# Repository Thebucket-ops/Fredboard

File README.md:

# ***THE FREDBOARD V1/V2***
fred is the seal

  The fredboard is a custom pi pico devboard:
  - the v2 has a MPU-6500 and has a reboot button with a led to indicate the restart;
  - the v1 (untested) allows to use all but one pins provided by the rp2040, and has a led to indicate when the devboard is powered

## **V2 (TO BE APPROVED)**

(Fred is the sea lion)

### **SCHEMATICS**
  Here's the schematic for the pcb, you can see the whole project from /v2/PCB

### **THE PCB**
  This is the pcb, front and back (image art can be found on /img/devboard):

### **PINOUT**
  Here's a diagram for the pinout of the v2, for more information on each pins capabilities, look up the rp2040 datasheet

### **BOM and Gerber**
  The Bill Of Materials and the Gerber files can be found in the /v2/PCB/production folder, these are the required materials:

 - 2 33pF 0402 capacitors
 - 13 0.1uF 0402 capacitors
 - 2 1uF 0402 capacitors
 - 2 10uF 0603 capacitors
 - 1 10 nF 0402 capacitor
 - 1 0402 white led
 - 1 USB_C_Receptacle_USB2.0_14P
 - 2 pinheaders 1x20 (optional)
 - 1 pinheader 1x3 (optional)
 - 2 0402 27 ohm resistors
 - 1 0402 150 ohm resistor
 - 3 0402 1K resistors
 - 2 0402 5.1K resistors
 - 1 0402 10K resistor
 - 2 SW_Push_SPST_NO_Alps_SKRK button
 - 1 RP2040
 - 1 MCP1700x-330xxTT
 - 1 W25Q16JVUXIQ TR flash memory
 - 1 Crystal_SMD_3225-4Pin_3.2x2.5mm
 - 1 MPU-6500

## **V1 (UNTESTED)**

### **SCHEMATICS**
  Here's the schematic for the pcb, you can see the whole project from /PCB

### **THE PCB**
  This is the pcb, front and back (image art can be found on /img/devboard):

### **BOM and Gerber**
  The Bill Of Materials and the Gerber files can be found in the /PCB/production folder, these are the required materials:

 - 10 0.1uF 0402 capacitors
 - 2 1uF 0402 capacitors
 - 2 10uF 0603 capacitors
 - 2 33pF 0402 capacitors
 - 1 0402 white led
 - 1 USB_C_Receptacle_USB2.0_14P
 - 2 pinheaders 1x20 (optional)
 - 1 pinheader 1x3 (optional)
 - 2 0402 5.1K resistors
 - 2 0402 27 ohm resistors
 - 2 0402 1K resistors
 - 1 0402 10K resistor
 - 1 SW_Push_SPST_NO_Alps_SKRK button
 - 1 RP2040
 - 1 MCP1700x-330xxTT
 - 1 W25Q16JVUXIQ TR flash memory
 - 1 Crystal_SMD_3225-4Pin_3.2x2.5mm

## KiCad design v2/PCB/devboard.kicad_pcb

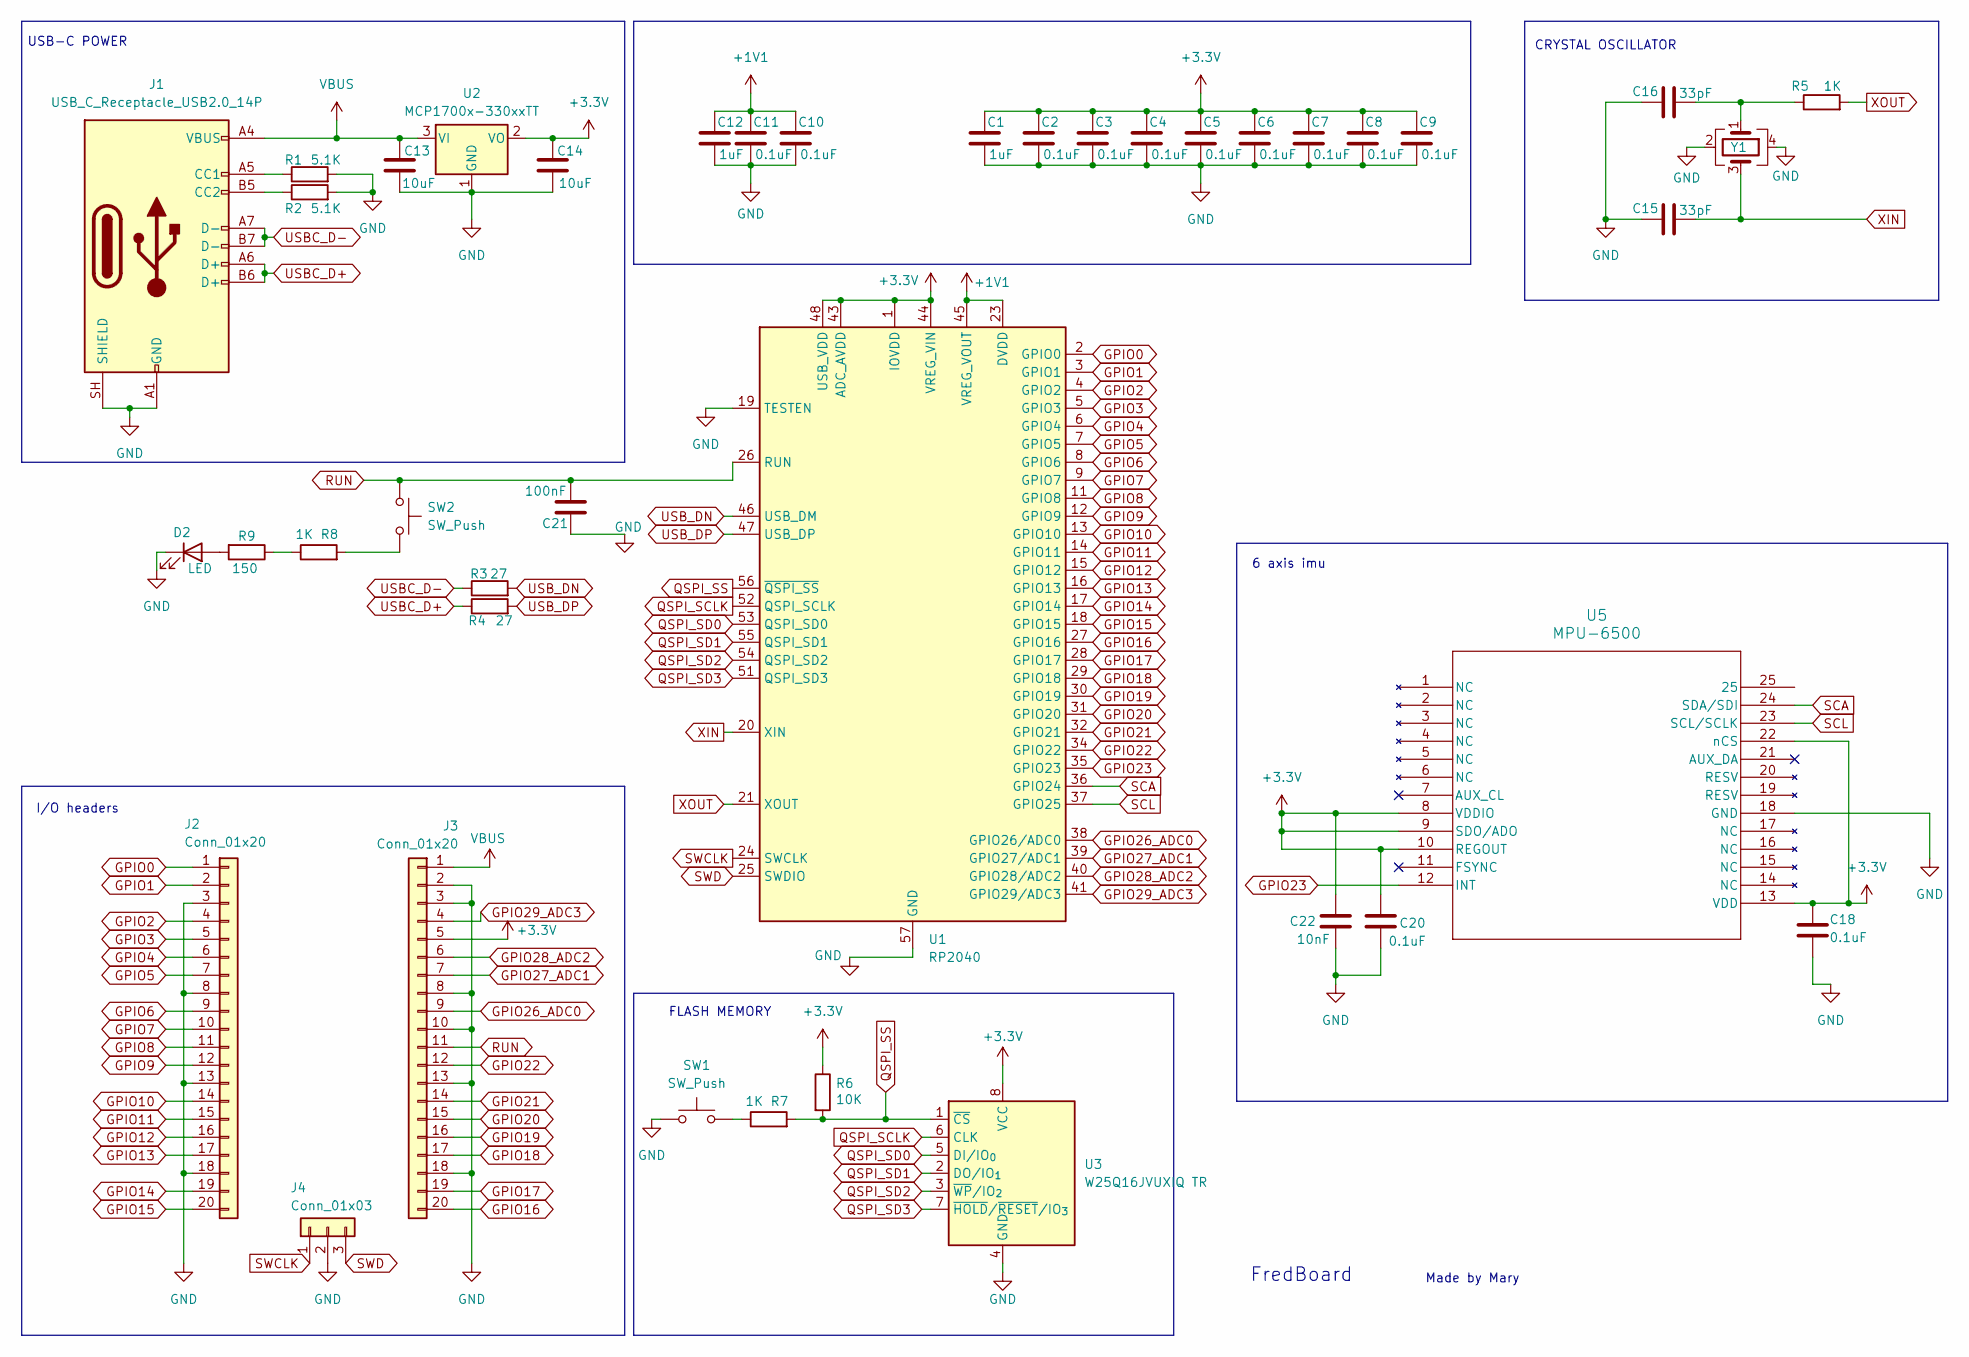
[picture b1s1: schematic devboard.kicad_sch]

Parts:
C1, C12: 1uF; C_0402_1005Metric
C2, C3, C4, C5, C6, C7, C8, C9, C10, C11, C18, C20: 0.1uF; C_0402_1005Metric
C13, C14: 10uF; C_0603_1608Metric
C15, C16: 33pF; C_0402_1005Metric
C21: 100nF; C_0402_1005Metric
C22: 10nF; C_0402_1005Metric
D2: LED; LED_0402_1005Metric
J1: USB_C_Receptacle_USB2.0_14P; USB_C_Receptacle_HRO_TYPE-C-31-M-12
J2, J3: Conn_01x20; PinHeader_1x20_P2.54mm_Vertical
J4: Conn_01x03; PinHeader_1x03_P2.54mm_Vertical
R1, R2: 5.1K; R_0402_1005Metric
R3, R4: 27; R_0402_1005Metric
R5, R7, R8: 1K; R_0402_1005Metric
R6: 10K; R_0402_1005Metric
R9: 150; R_0402_1005Metric
SW1, SW2: SW_Push; SW_Push_SPST_NO_Alps_SKRK
U1: RP2040; QFN-56-1EP_7x7mm_P0.4mm_EP3.2x3.2mm
U2: MCP1700x-330xxTT; SOT-23
U3: W25Q16JVUXIQ TR; Winbond_USON-8-1EP_3x2mm_P0.5mm_EP0.2x1.6mm
U5: MPU-6500; QFN24_3X3X0P9_IVS
Y1: Crystal_GND24; Crystal_SMD_3225-4Pin_3.2x2.5mm

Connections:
+1V1: C10.1, C11.1, C12.1, U1.23 (DVDD), U1.45 (VREG_VOUT), U1.50 (DVDD)
+3.3V: C1.1, C2.1, C3.1, C4.1, C5.1, C6.1, C7.1, C8.1, C9.1, C14.1, C18.1, C20.1, C22.1, J3.5, R6.1, U1.1 (IOVDD), U1.10 (IOVDD), U1.22 (IOVDD), U1.33 (IOVDD), U1.42 (IOVDD), U1.43 (ADC_AVDD), U1.44 (VREG_VIN), U1.48 (USB_VDD), U1.49 (IOVDD), U2.2 (VO), U3.8 (VCC), U5.8 (VDDIO), U5.9 (SDO/ADO), U5.10 (REGOUT), U5.13 (VDD), U5.22 (nCS)
GND: C1.2, C2.2, C3.2, C4.2, C5.2, C6.2, C7.2, C8.2, C9.2, C10.2, C11.2, C12.2, C13.2, C14.2, C15.1, C16.1, C18.2, C20.2, C21.1, C22.2, D2.1 (K), J1.A1 (GND), J1.A12 (GND), J1.B1 (GND), J1.B12 (GND), J1.SH (SHIELD), J2.3, J2.8, J2.13, J2.18, J3.2, J3.3, J3.8, J3.10, J3.13, J3.18, J4.2, R1.2, R2.2, SW1.1, U1.19 (TESTEN), U1.57 (GND), U2.1 (GND), U3.4 (GND), U5.18 (GND), Y1.2 (G), Y1.4 (G)
GPIO0: J2.1, U1.2 (GPIO0)
GPIO1: J2.2, U1.3 (GPIO1)
GPIO2: J2.4, U1.4 (GPIO2)
GPIO3: J2.5, U1.5 (GPIO3)
GPIO4: J2.6, U1.6 (GPIO4)
GPIO5: J2.7, U1.7 (GPIO5)
GPIO6: J2.9, U1.8 (GPIO6)
GPIO7: J2.10, U1.9 (GPIO7)
GPIO8: J2.11, U1.11 (GPIO8)
GPIO9: J2.12, U1.12 (GPIO9)
GPIO10: J2.14, U1.13 (GPIO10)
GPIO11: J2.15, U1.14 (GPIO11)
GPIO12: J2.16, U1.15 (GPIO12)
GPIO13: J2.17, U1.16 (GPIO13)
GPIO14: J2.19, U1.17 (GPIO14)
GPIO15: J2.20, U1.18 (GPIO15)
GPIO16: J3.20, U1.27 (GPIO16)
GPIO17: J3.19, U1.28 (GPIO17)
GPIO18: J3.17, U1.29 (GPIO18)
GPIO19: J3.16, U1.30 (GPIO19)
GPIO20: J3.15, U1.31 (GPIO20)
GPIO21: J3.14, U1.32 (GPIO21)
GPIO22: J3.12, U1.34 (GPIO22)
GPIO23: U1.35 (GPIO23), U5.12 (INT)
GPIO26_ADC0: J3.9, U1.38 (GPIO26/ADC0)
GPIO27_ADC1: J3.7, U1.39 (GPIO27/ADC1)
GPIO28_ADC2: J3.6, U1.40 (GPIO28/ADC2)
GPIO29_ADC3: J3.4, U1.41 (GPIO29/ADC3)
unnamed: C16.2, R5.1, Y1.1
unnamed: D2.2 (A), R9.2
unnamed: J1.A5 (CC1), R1.1
unnamed: J1.B5 (CC2), R2.1
unnamed: R7.1, SW1.2
unnamed: R8.1, R9.1
unnamed: R8.2, SW2.2
QSPI_SCLK: U1.52 (QSPI_SCLK), U3.6 (CLK)
QSPI_SD0: U1.53 (QSPI_SD0), U3.5 (DI/IO_{0})
QSPI_SD1: U1.55 (QSPI_SD1), U3.2 (DO/IO_{1})
QSPI_SD2: U1.54 (QSPI_SD2), U3.3 (~WP/IO_{2})
QSPI_SD3: U1.51 (QSPI_SD3), U3.7 (~HOLD/~RESET/IO_{3})
QSPI_SS: R6.2, R7.2, U1.56 (~QSPI_SS), U3.1 (~CS)
RUN: C21.2, J3.11, SW2.1, U1.26 (RUN)
SCA: U1.36 (GPIO24), U5.24 (SDA/SDI)
SCL: U1.37 (GPIO25), U5.23 (SCL/SCLK)
SWCLK: J4.1, U1.24 (SWCLK)
SWD: J4.3, U1.25 (SWDIO)
USBC_D+: J1.A6 (D+), J1.B6 (D+), R4.1
USBC_D-: J1.A7 (D-), J1.B7 (D-), R3.1
USB_DN: R3.2, U1.46 (USB_DM)
USB_DP: R4.2, U1.47 (USB_DP)
VBUS: C13.1, J1.A4 (VBUS), J1.A9 (VBUS), J1.B4 (VBUS), J1.B9 (VBUS), J3.1, U2.3 (VI)
XIN: C15.2, U1.20 (XIN), Y1.3
XOUT: R5.2, U1.21 (XOUT)

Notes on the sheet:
FLASH MEMORY
CRYSTAL OSCILLATOR
USB-C POWER
Made by Mary
FredBoard
6 axis imu
I/O headers

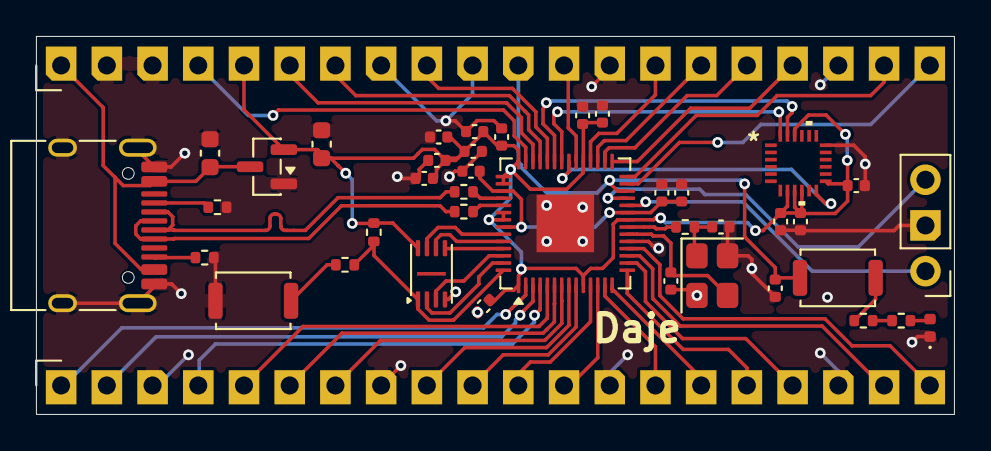
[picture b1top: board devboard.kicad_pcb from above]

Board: 2 copper layers, 51.0 x 21.0 mm, 41 parts (0 on the bottom side), 56 nets.

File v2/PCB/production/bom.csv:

Designator,Footprint,Quantity,Value,LCSC Part #
"C1, C12",0402,2,1uF,
"C10, C11, C18, C2, C20, C3, C4, C5, C6, C7, C8, C9",0402,12,0.1uF,
"C13, C14",0603,2,10uF,
"C15, C16",0402,2,33pF,
C21,0402,1,100nF,
C22,0402,1,10nF,
D2,0402,1,LED,
J1,USB_C_Receptacle_HRO_TYPE-C-31-M-12,1,USB_C_Receptacle_USB2.0_14P,
"J2, J3",PinHeader_1x20_P2.54mm_Vertical,2,Conn_01x20,
J4,PinHeader_1x03_P2.54mm_Vertical,1,Conn_01x03,
"R1, R2",0402,2,5.1K,
"R3, R4",0402,2,27,
"R5, R7, R8",0402,3,1K,
R6,0402,1,10K,
R9,0402,1,150,
"SW1, SW2",SW_Push_SPST_NO_Alps_SKRK,2,SW_Push,
U1,QFN-56-1EP_7x7mm_P0.4mm_EP3.2x3.2mm,1,RP2040,
U2,SOT-23,1,MCP1700x-330xxTT,
U3,Winbond_USON-8-1EP_3x2mm_P0.5mm_EP0.2x1.6mm,1,W25Q16JVUXIQ TR,
U5,QFN24_3X3X0P9_IVS,1,MPU-6500,
Y1,Crystal_SMD_3225-4Pin_3.2x2.5mm,1,Crystal_GND24,

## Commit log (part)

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2026-06-19 reordering repo
2026-06-19 updating readme and pcb
2026-06-20 Create LICENSE
2026-06-27 added v1 folder
    added leds to the v1 board and created a v2 folder
